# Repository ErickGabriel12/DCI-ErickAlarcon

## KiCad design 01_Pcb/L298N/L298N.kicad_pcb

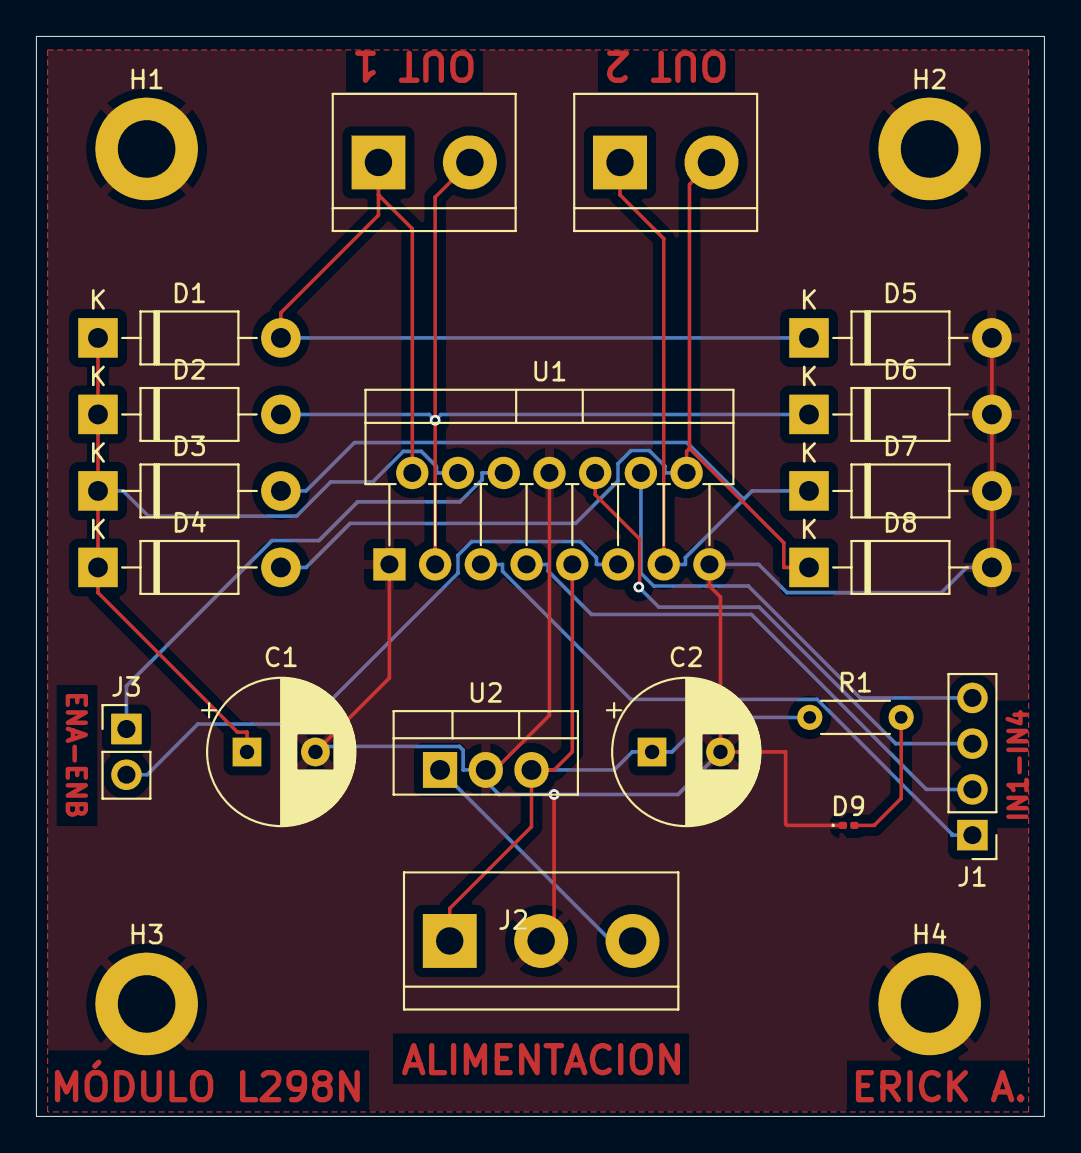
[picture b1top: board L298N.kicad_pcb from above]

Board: 2 copper layers, 56.0 x 60.0 mm, 23 parts (0 on the bottom side), 15 nets.

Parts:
C1, C2: 220UF; CP_Radial_D8.0mm_P3.80mm
D1, D2, D3, D4, D5, D6, D7, D8: 1N4007; D_DO-41_SOD81_P10.16mm_Horizontal
D9: LED; LED_0201_0603Metric
H1, H2, H3, H4: MountingHole_3.2mm_M3_ISO7380_Pad
J1: Conn_01x04_Pin; PinHeader_1x04_P2.54mm_Vertical
J2: Screw_Terminal_01x03; TerminalBlock_bornier-3_P5.08mm
J3: Conn_01x02_Pin; PinHeader_1x02_P2.54mm_Vertical
J6: SALIDA 1; TerminalBlock_bornier-2_P5.08mm
J7: SALIDA 2; TerminalBlock_bornier-2_P5.08mm
R1: 1K; R_Axial_DIN0204_L3.6mm_D1.6mm_P5.08mm_Horizontal
U1: L298N; TO-220-15_P2.54x2.54mm_StaggerOdd_Lead4.58mm_Vertical
U2: LM78M05_TO220; TO-220-3_Vertical

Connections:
5V: C2.1, J2.1, R1.1, U1.9 (Vss), U2.3 (VO)
ENA: J3.1, U1.6 (EnA)
ENB: J3.2, U1.11 (EnB)
GND: C1.2, C2.2, D5.2 (A), D6.2 (A), D7.2 (A), D8.2 (A), D9.1 (K), H1.1, H2.1, H3.1, H4.1, J2.2, U1.1 (SENSE_A), U1.8 (GND), U1.15 (SENSE_B), U2.2 (GND)
IN1: J1.1, U1.5 (IN1)
IN2: J1.2, U1.7 (IN2)
IN3: J1.3, U1.10 (IN3)
IN4: J1.4, U1.12 (IN4)
unnamed: C1.1, D1.1 (K), D2.1 (K), D3.1 (K), D4.1 (K), U1.4 (Vs)
unnamed: D9.2 (A), R1.2
OUT1: D1.2 (A), D5.1 (K), J6.1, U1.2 (OUT1)
OUT2: D2.2 (A), D6.1 (K), J6.2, U1.3 (OUT2)
OUT3: D3.2 (A), D7.1 (K), J7.1, U1.13 (OUT3)
OUT4: D4.2 (A), D8.1 (K), J7.2, U1.14 (OUT4)
V+: J2.3, U2.1 (VI)

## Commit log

2025-03-11 template
2025-04-29 Tarea Modulo L298N
